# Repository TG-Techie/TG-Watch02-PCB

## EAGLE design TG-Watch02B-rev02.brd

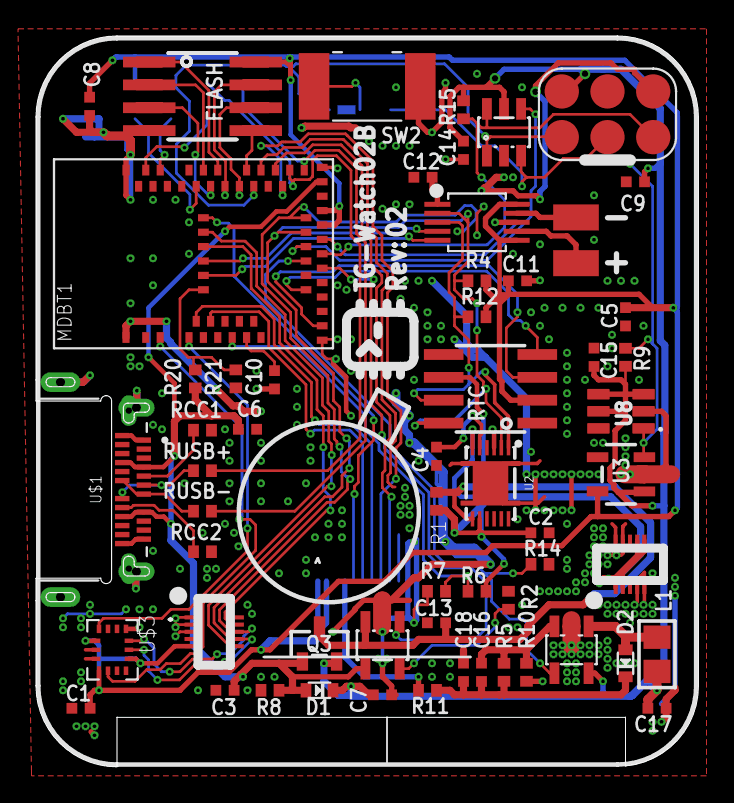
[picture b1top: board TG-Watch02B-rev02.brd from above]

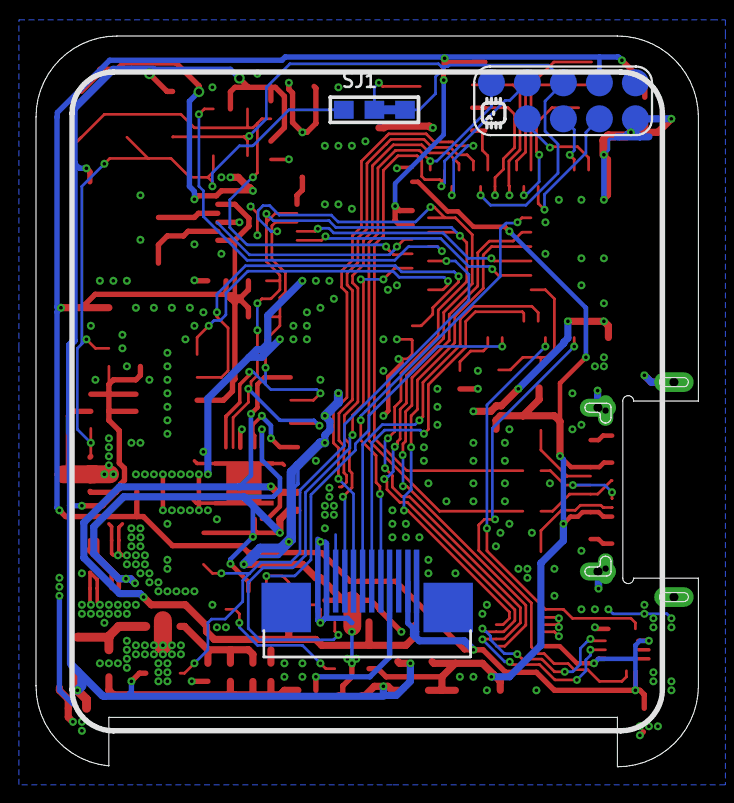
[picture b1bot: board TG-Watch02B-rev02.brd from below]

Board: 2 copper layers, 36.8 x 40.6 mm, 62 parts (2 on the bottom side), 55 nets.

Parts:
02: TG-Watch02B; TG-PROD-LABEL-5MM
C1, C18: 4.7uf; MICROBUILDER__0402_NODIMS
C2, C4, C11, C12: 1uf; MICROBUILDER__0402_NODIMS
C3, C5, C6, C7, C8, C9, C13, C14, C15, C17: 10uf; MICROBUILDER__0402_NODIMS
C10: 0.1uF; MICROBUILDER__0402_NODIMS
C16: 0.1nF; MICROBUILDER__0402_NODIMS
D1: MBR120; SOD-523
D2: BAT54T1G; SOD-523
FLASH: W25Q128JVSIQ TR; SOIC8_208MIL
HEDR2: 1X02SMD; 1X2_SMD
IC3: W25Q128JVSIQ TR; SOIC8_150MIL
ISP1: CON-ICSP/ISP-AVR-POGO; 2X3_POGO_AVR
L1: 10uH; 0805
MDBT1: MDBT50
Q3: DMG2305; SOT23-R
R1: .01 ohm; TG_0402
R2: 2k; TG_0402
R4, R8, R9, R12, R21: 100k; TG_0402
R5: 68k; TG_0402
R6: 270k; TG_0402
R7: 330k; TG_0402
R10, R14, R15: 10k; TG_0402
R11: 220K; TG_0402
R20: 51k; TG_0402
RCC1, RCC2: 5.1k; TG_0402
RTC: SEN-TIME-DS3231-(PERSICION-TEMP); SOIC8_150MIL
RUSB+: 22ohm; TG_0402
RUSB-: 22ohm; TG_0402
SJ1: SOLDERJUMPER_2WAY_OPEN_0603
SW2: BTN_CK_KSS
U1: MICROBUILDER_PSOP10
U2: BQ27441-G1; PDSO-N12
U3: SOT23-5
U4: FAN5331SX; SOT23-5@1
U7: DISP_1.54_LCMTF15423A-C_LCD+CAPTCH_ASSEMBLY_DUALS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; TF-LCM15423A-C_DUALSIDE
U8: UNDERVOLT-TPS3702CX3; SOT95P280X110-6N
U9: MCP73831/OT; SOT23-5L
U10: MCU-ATTINY10; SOT23-6
U$1: USB-C-CON-TG_MOD-2295018-2.0; TG_RM_TE_2295018-2
U$3: MICROBUILDER_LSM6DSOX; MICROBUILDER_LGA-14L
U$11: CON-BAT-TG-MEZ_FEMALE; MEZ-DF37NC-10DS
U$13: CON_SWD_POGO_USB; SWD_POGO_USB

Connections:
1.8V: C4.2, U2.5
3V3: C1.2, C5.2, C8.2, C11.2, FLASH.8, IC3.8, MDBT1.28, MDBT1.30, R4.2, R12.2, RTC.2, U1.6, U1.10, U3.5, U7.FPC11, U7.FPC12, U7.MEZ5, U$3.5, U$3.8, U$3.12, U$13.6
9.6V: C16.1, C18.1, D2.K, R5.2, R11.2
ACCEL_INT1: MDBT1.4, U$3.4
ACCEL_INT2: MDBT1.3, U$3.9
AREF: C10.2, MDBT1.12
BAT_CHRG_SET: R2.2, U9.5
CC1: RCC1.2, U$1.A5
CC2: RCC2.2, U$1.B5
D5_REQ_PWR_RST: MDBT1.25, U10.4
D6_BACKLIGHT: MDBT1.23, R14.2, U4.4
D9_RTC_RESET: MDBT1.19, RTC.4
D10_RTC_INT: MDBT1.16, RTC.3
D11_CHRG_STAT: MDBT1.22, U9.1
D12_SMC_RESET: ISP1.5, MDBT1.24, R15.2, U10.6
D14_VBUS_PRESENT: MDBT1.56, R20.1, R21.2
D15_HAPTIC_ENABLE: MDBT1.57, U1.5
D16_HAPTIC_INT: MDBT1.58, U1.4
D17_CTP_INT: MDBT1.59, U7.MEZ9
D18_CTP_RESET: MDBT1.60, U7.MEZ6
D19_TFT_RESET: MDBT1.61, U7.FPC8
D20_TFT_DC: MDBT1.5, U7.FPC6
D22_TFT_CS: MDBT1.7, U7.FPC7
D+: MDBT1.35, RUSB+.1, U$13.8
D-: MDBT1.34, RUSB-.1, U$13.9
DRV_REG: C12.2, U1.1
GND: C1.1, C2.1, C3.1, C4.1, C5.1, C6.1, C7.1, C8.1, C9.2, C10.1, C11.1, C12.1, C13.1, C14.1, C15.1, C17.1, C18.2, FLASH.4, IC3.4, ISP1.6, MDBT1.1, MDBT1.2, MDBT1.15, MDBT1.33, MDBT1.55, R2.1, R7.1, R8.1, R10.1, R14.1, R21.1, RCC1.1, RCC2.1, RTC.5, SW2.P$1, U1.8, U2.3, U2.EP, U2.EP1, U2.EP2, U2.EP3, U2.EP4, U3.2, U4.2, U7.FPC1, U7.FPC2, U7.FPC10, U7.MEZ1, U7.MEZ2, U7.MEZ3, U8.2, U9.2, U10.2, U$1.A1, U$1.A12, U$1.B1, U$1.B12, U$1.P1_1, U$1.P1_2, U$1.P2_1, U$1.P2_2, U$1.P4, U$1.P5, U$3.1, U$3.6, U$3.7, U$11.P$4, U$11.P$5, U$11.P$9, U$11.P$10, U$13.1, U$13.5
HAPTIC+: HEDR2.1, U1.7
HAPTIC-: HEDR2.2, U1.9
MOSI: MDBT1.37, U7.FPC4
unnamed: C16.2, R5.1, R10.2, U4.3
unnamed: D2.A, L1.2, U4.1
unnamed: SJ1.2, SW2.P$2
QSPI_CS: FLASH.1, IC3.1, MDBT1.44
QSPI_DATA0: FLASH.5, IC3.5, MDBT1.41
QSPI_DATA1: FLASH.2, IC3.2, MDBT1.46
QSPI_DATA2: FLASH.3, IC3.3, MDBT1.45
QSPI_DATA3: FLASH.7, IC3.7, MDBT1.43
QSPI_SCK: FLASH.6, IC3.6, MDBT1.42
RESET: ISP1.1, MDBT1.40, SJ1.3, U10.1, U$13.7
SCK: MDBT1.36, U7.FPC5
SCL: MDBT1.27, R4.1, RTC.8, U1.2, U2.2, U7.MEZ7, U$3.13
SDA: MDBT1.29, R12.1, RTC.7, U1.3, U2.1, U7.MEZ8, U$3.14
SWDCLK: MDBT1.53, U$13.4
SWDIO: MDBT1.51, U$13.3
SWO: MDBT1.47, U$13.2
SYSON_TPICLK: ISP1.3, R9.1, SJ1.1, U3.3, U8.1, U10.3
USBD+: RUSB+.2, U$1.A6, U$1.B6
USBD-: RUSB-.2, U$1.A7, U$1.B7
VBAT: C13.2, Q3.3, R1.1, RTC.6, U2.7, U9.3
VBAT_RAW: C2.2, R1.2, R6.2, U2.6, U2.8, U$11.P$1, U$11.P$2, U$11.P$6, U$11.P$7
VBUS: C3.2, C6.2, D1.A, MDBT1.32, Q3.1, R8.2, R20.2, U9.4, U$1.A4, U$1.A9, U$1.B4, U$1.B9
VDIV: MDBT1.10, R6.1, R7.2
VLED: R11.1, U7.FPC9
VSORS: C7.2, C9.1, C14.2, C15.2, C17.2, D1.K, ISP1.2, L1.1, Q3.2, R9.2, R15.1, U3.1, U4.5, U8.3, U8.4, U8.5, U10.5

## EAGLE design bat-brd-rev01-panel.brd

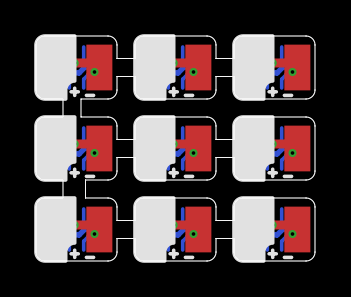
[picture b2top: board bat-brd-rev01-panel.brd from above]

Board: 2 copper layers, 15.5 x 12.5 mm, 18 parts (0 on the bottom side), 18 nets.

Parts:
HEDR1, HEDR2, HEDR3, HEDR4, HEDR5, HEDR6, HEDR7, HEDR8, HEDR9: 1X02SMD; 1X2_SMD
U$1, U$2, U$3, U$4, U$5, U$6, U$7, U$8, U$9: CON-BAT-TG-MEZ_MALE; MEZ-DF37C-10DP

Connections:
GND: HEDR1.2, U$1.P$4, U$1.P$5, U$1.P$9, U$1.P$10
GND1: HEDR2.2, U$2.P$4, U$2.P$5, U$2.P$9, U$2.P$10
GND2: HEDR3.2, U$3.P$4, U$3.P$5, U$3.P$9, U$3.P$10
GND3: HEDR4.2, U$4.P$4, U$4.P$5, U$4.P$9, U$4.P$10
GND4: HEDR5.2, U$5.P$4, U$5.P$5, U$5.P$9, U$5.P$10
GND5: HEDR6.2, U$6.P$4, U$6.P$5, U$6.P$9, U$6.P$10
GND6: HEDR7.2, U$7.P$4, U$7.P$5, U$7.P$9, U$7.P$10
GND7: HEDR8.2, U$8.P$4, U$8.P$5, U$8.P$9, U$8.P$10
GND8: HEDR9.2, U$9.P$4, U$9.P$5, U$9.P$9, U$9.P$10
VBAT: HEDR1.1, U$1.P$1, U$1.P$2, U$1.P$6, U$1.P$7
VBAT1: HEDR2.1, U$2.P$1, U$2.P$2, U$2.P$6, U$2.P$7
VBAT2: HEDR3.1, U$3.P$1, U$3.P$2, U$3.P$6, U$3.P$7
VBAT3: HEDR4.1, U$4.P$1, U$4.P$2, U$4.P$6, U$4.P$7
VBAT4: HEDR5.1, U$5.P$1, U$5.P$2, U$5.P$6, U$5.P$7
VBAT5: HEDR6.1, U$6.P$1, U$6.P$2, U$6.P$6, U$6.P$7
VBAT6: HEDR7.1, U$7.P$1, U$7.P$2, U$7.P$6, U$7.P$7
VBAT7: HEDR8.1, U$8.P$1, U$8.P$2, U$8.P$6, U$8.P$7
VBAT8: HEDR9.1, U$9.P$1, U$9.P$2, U$9.P$6, U$9.P$7

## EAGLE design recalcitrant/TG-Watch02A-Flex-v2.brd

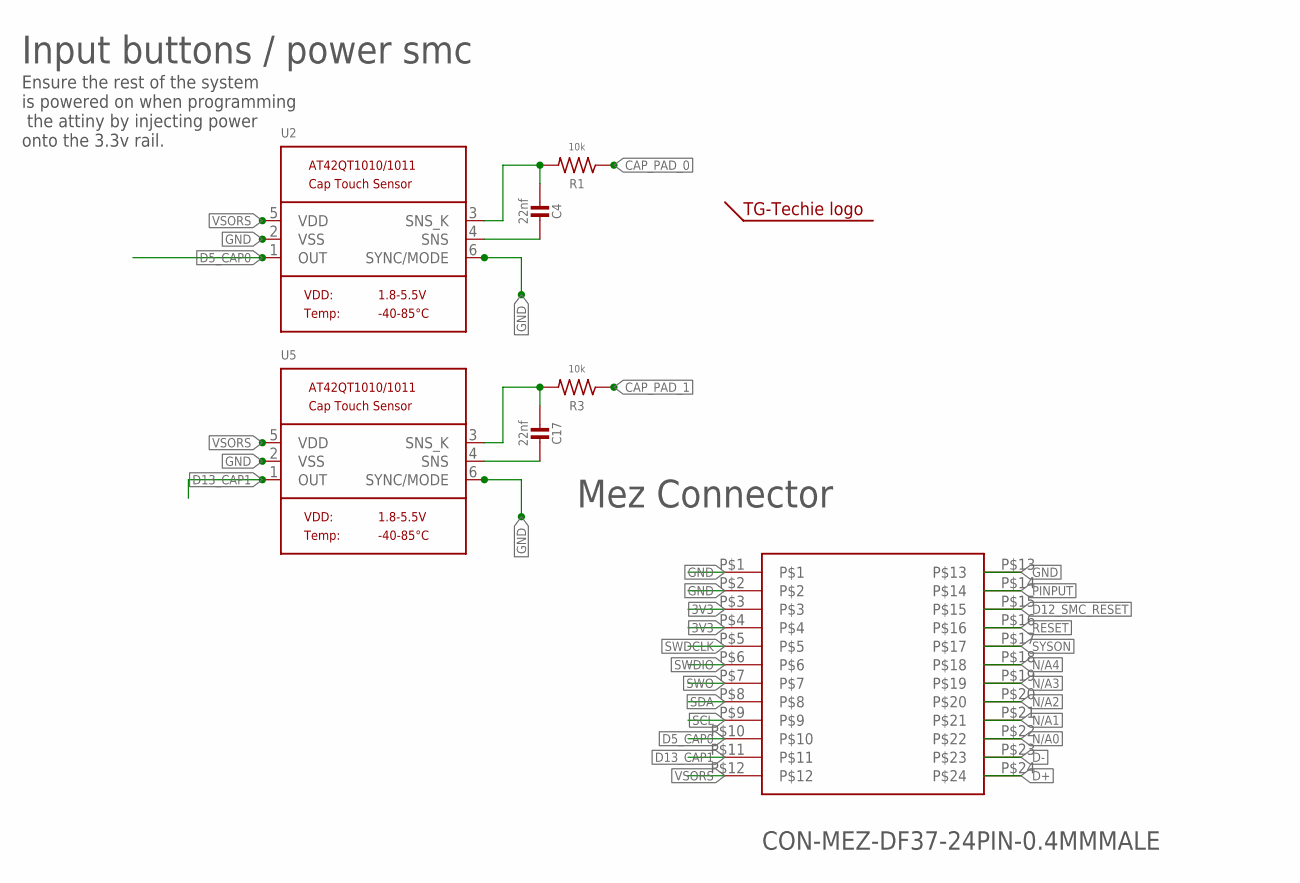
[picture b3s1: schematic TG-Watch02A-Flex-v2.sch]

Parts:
C4, C17: 22nf; _0402
R1, R3: 10k; TG_0402
U2, U5: SEN-CAPTOUCH-AT42QT1010/1; MICROBUILDER_SOT23-6
U$1: LOGO-TG-TECHIE2.5MM-SYMB; TG-LOGO-2.5MM-SYMB
U$11: CON-MEZ-DF37-24PIN-0.4MMMALE; MEZ-DF37B-24DP

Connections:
3V3: U$11.P$3, U$11.P$4
CAP_PAD_0: R1.1
CAP_PAD_1: R3.1
D5_CAP0: U2.1 (OUT), U$11.P$10
D12_SMC_RESET: U$11.P$15
D13_CAP1: U5.1 (OUT), U$11.P$11
D+: U$11.P$24
D-: U$11.P$23
GND: U2.2 (VSS), U2.6 (SYNC/MODE), U5.2 (VSS), U5.6 (SYNC/MODE), U$11.P$1, U$11.P$2, U$11.P$13
unnamed: C4.1, U2.4 (SNS)
unnamed: C4.2, R1.2, U2.3 (SNS_K)
unnamed: C17.1, U5.4 (SNS)
unnamed: C17.2, R3.2, U5.3 (SNS_K)
N/A0: U$11.P$22
N/A1: U$11.P$21
N/A2: U$11.P$20
N/A3: U$11.P$19
N/A4: U$11.P$18
PINPUT: U$11.P$14
RESET: U$11.P$16
SCL: U$11.P$9
SDA: U$11.P$8
SWDCLK: U$11.P$5
SWDIO: U$11.P$6
SWO: U$11.P$7
SYSON: U$11.P$17
VSORS: U2.5 (VDD), U5.5 (VDD), U$11.P$12

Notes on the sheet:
Input buttons / power smc
Ensure the rest of the system is powered on when programming the attiny by injecting power onto the 3.3v rail.
Mez Connector

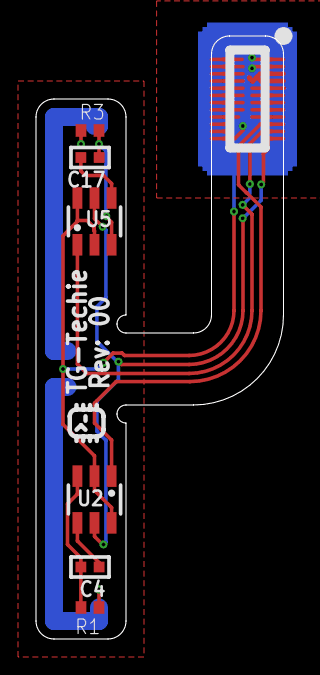
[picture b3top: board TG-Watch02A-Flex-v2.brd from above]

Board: 2 copper layers, 13.8 x 33.5 mm, 8 parts (0 on the bottom side), 9 nets.

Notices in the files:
parts and their libraries:
microbuilder: This work is placed in the public domain, and may be freely used for commercial and non-commercial work with the following conditions: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
